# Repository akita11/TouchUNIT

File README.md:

# TouchUNIT

タッチセンサICの[TTP223N-HA6](https://www.lcsc.com/product-detail/Touch-Sensors_Tontek-Design-Tech-TTP223N-HA6_C93723.html)を使用した、2系統のタッチセンサです。Grove端子の2本の信号線にタッチ状態を出力することができます。M5Stackの2個の物理スイッチがある[デュアルボタンUNIT](https://www.switch-science.com/products/4048)と同等の出力のため、UIFlow等ではこのデュアルボタンUNIT用のブロック・プログラムがそのまま使えます。

※[M5Stack用ADCユニット](https://www.switch-science.com/products/9491)と形状が互換なので、そのケースを流用できます。

## 使い方

オレンジのネジ端子にタッチ電極を接続します。T1とT2の独立の2系統のタッチ検出を使用できます。手を近づけただけでONとなるなどタッチ検出の感度が高すぎる場合は、後述の方法で感度を調整してください。（標準状態より感度を高めることは原理上できません）

## 設定の変更

### タッチ検出の感度の変更

基板上にコンデンサを取り付けることで、タッチ検出の感度を調整（低くする）ことができます。実際の使用状況にあわせて、適切な容量のコンデンサを接続してください。容量値や動作原理などはタッチ検出IC(TTP223N)のデータシートを参照してください。

- T1 : C3（1608サイズ表面実装）またはC4（挿入実装）
- T2 : C5（1608サイズ表面実装）またはC6（挿入実装）

### 出力信号の極性・トグルの設定

基板裏面の半田ジャンパによって、出力の動作モードを設定できます。詳細はタッチ検出IC(TTP223N)のデータシートと回路図を参照してください。

- POL1(JP1/T1用)/POL2(JP3/T2用): ショート（標準設定）=タッチ時'0'／開放（パターンカット）=タッチ時'1'
- TOG1(JP2/T1用)/TOG2(JP4/T2用): 開放（標準設定）=タッチ時のみ0/1／ショート（半田を盛る）=タッチごとに出力がトグル

## Author

Junichi Akita (akita@ifdl.jp, @akita11)

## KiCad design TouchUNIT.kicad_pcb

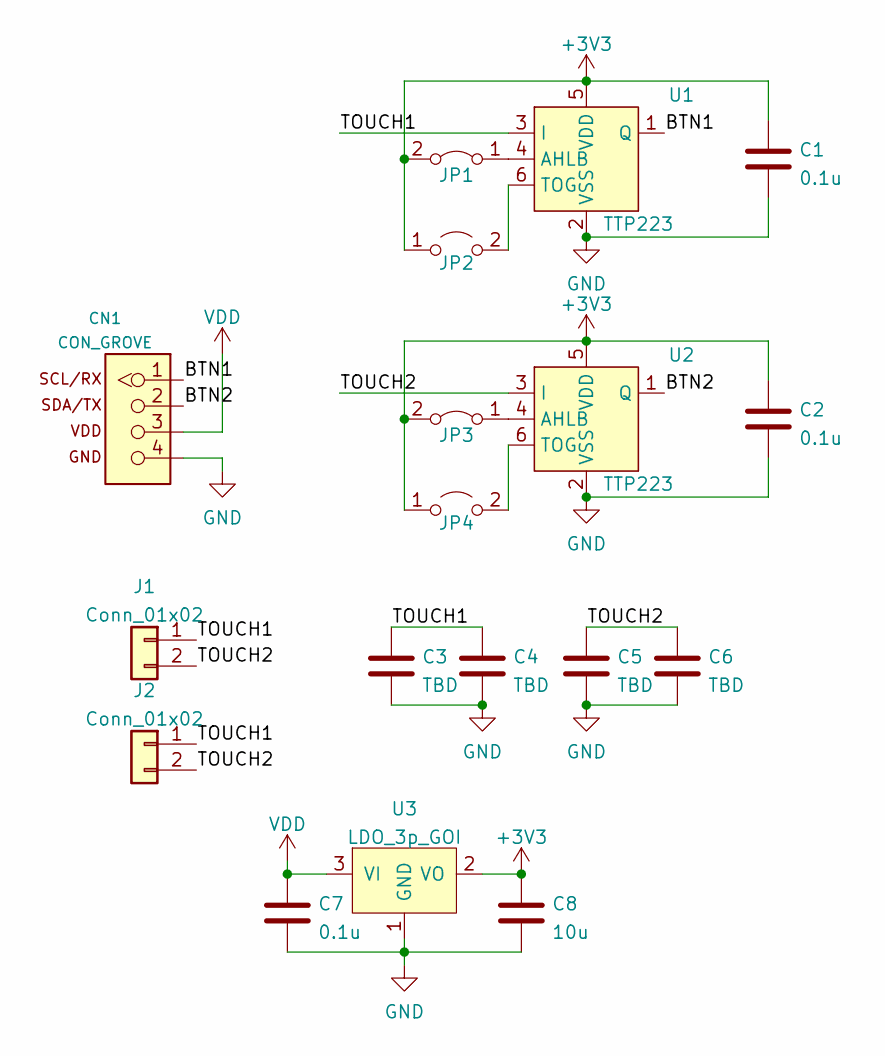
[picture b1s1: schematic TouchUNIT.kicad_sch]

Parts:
C1, C2, C7: 0.1u; C_0603_1608Metric
C3, C5: TBD; C_0603_1608Metric
C4, C6: TBD; C_Disc_D3.0mm_W1.6mm_P2.50mm
C8: 10u; C_0603_1608Metric
CN1: CON_GROVE; CON_GROVE_H
J1: Conn_01x02; CON_HT396R_2P
J2: Conn_01x02; PinSocket_1x02_P2.54mm_Vertical
JP1, JP3: Jumper_2_Bridged; SolderJumper-2_P1.3mm_Bridged2Bar_Pad1.0x1.5mm
JP2, JP4: Jumper_2_Open; SolderJumper-2_P1.3mm_Open_Pad1.0x1.5mm
U1, U2: TTP223; SOT-23-6
U3: LDO_3p_GOI; SOT-23

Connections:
+3V3: C1.1, C2.1, C8.1, JP1.2 (B), JP2.1 (A), JP3.2 (B), JP4.1 (A), U1.5 (VDD), U2.5 (VDD), U3.2 (VO)
/BTN1: CN1.1, U1.1 (Q)
/BTN2: CN1.2, U2.1 (Q)
/TOUCH1: C3.1, C4.1, J1.1, J2.1, U1.3 (I)
/TOUCH2: C5.1, C6.1, J1.2, J2.2, U2.3 (I)
GND: C1.2, C2.2, C3.2, C4.2, C5.2, C6.2, C7.2, C8.2, CN1.4, U1.2 (VSS), U2.2 (VSS), U3.1 (GND)
unnamed: JP1.1 (A), U1.4 (AHLB)
unnamed: JP2.2 (B), U1.6 (TOG)
unnamed: JP3.1 (A), U2.4 (AHLB)
unnamed: JP4.2 (B), U2.6 (TOG)
VDD: C7.1, CN1.3, U3.3 (VI)

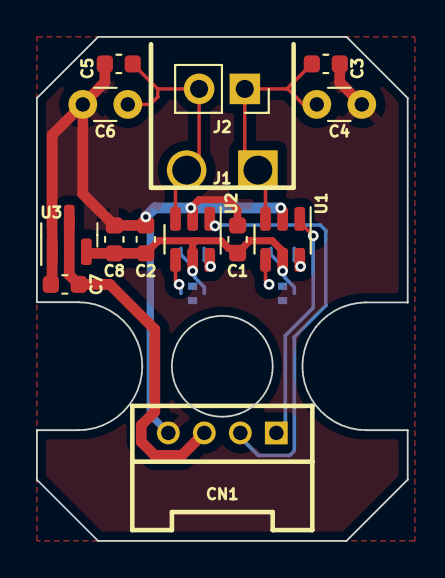
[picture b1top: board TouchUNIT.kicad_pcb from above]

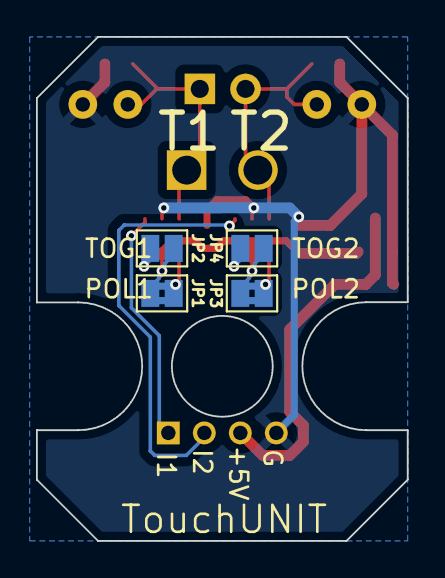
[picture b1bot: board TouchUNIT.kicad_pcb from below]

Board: 2 copper layers, 20.6 x 28.0 mm, 18 parts (4 on the bottom side), 11 nets.

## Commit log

2024-12-04 tentative initial commit
